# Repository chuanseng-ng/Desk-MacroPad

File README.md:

# Desk MacroPad
 Desk Macro-Pad inspired by PikaTea FK1

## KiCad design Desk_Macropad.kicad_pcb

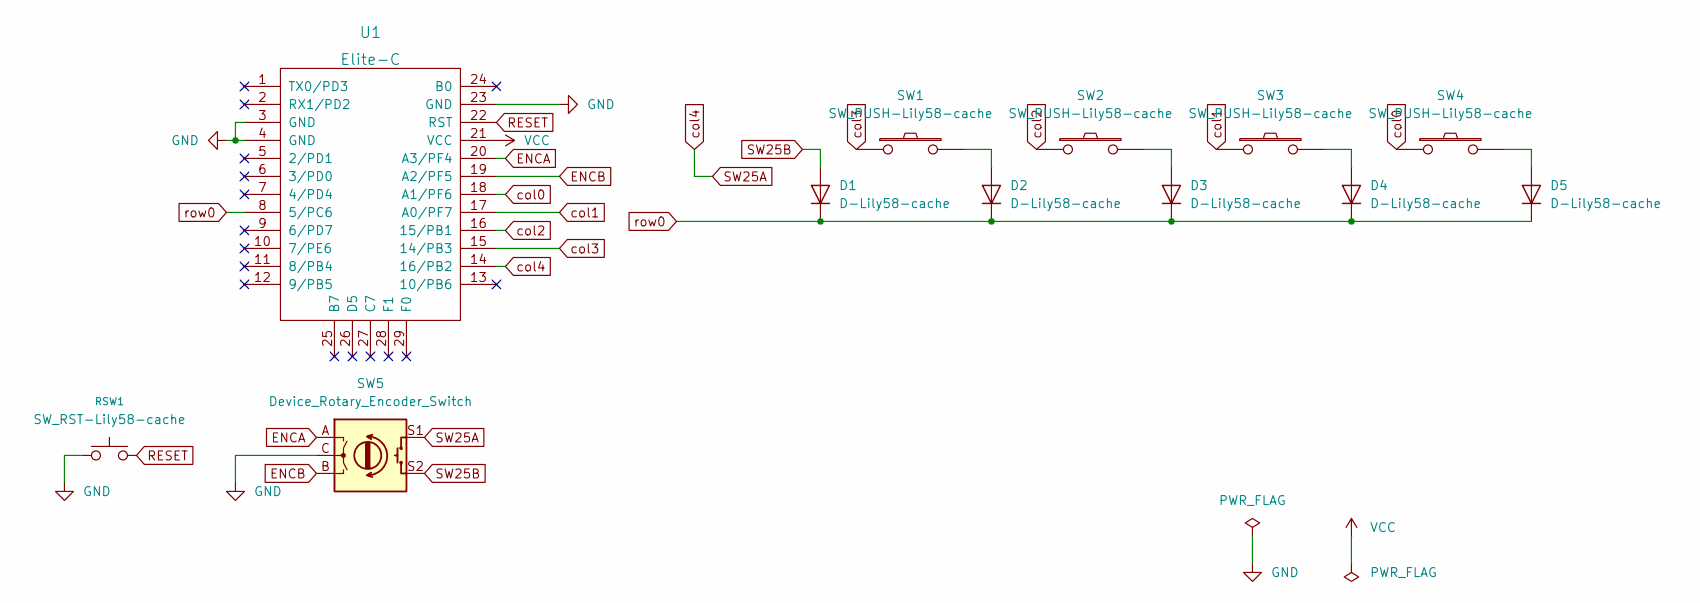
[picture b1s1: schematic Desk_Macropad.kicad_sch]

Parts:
D1, D2, D3, D4, D5: D-Lily58-cache; Diode_SOD123
RSW1: SW_RST-Lily58-cache; TACT_SWITCH_TVBP06
SW1, SW2, SW3, SW4: SW_PUSH-Lily58-cache; CherryMX_Hotswap
SW5: Device_Rotary_Encoder_Switch; RotaryEncoder_Alps_EC11E-Switch_Vertical_H20mm-keebio_modif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
U1: Elite-C

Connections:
ENCA: SW5.A, U1.20 (A3/PF4)
ENCB: SW5.B, U1.19 (A2/PF5)
GND: RSW1.1, SW5.C, U1.3 (GND), U1.4 (GND), U1.23 (GND)
unnamed: D2.2 (A), SW1.2
unnamed: D3.2 (A), SW2.2
unnamed: D4.2 (A), SW3.2
unnamed: D5.2 (A), SW4.2
RESET: RSW1.2, U1.22 (RST)
SW25A: SW5.S1, U1.14 (16/PB2)
SW25B: D1.2 (A), SW5.S2
VCC: U1.21 (VCC)
col0: SW4.1, U1.18 (A1/PF6)
col1: SW3.1, U1.17 (A0/PF7)
col2: SW2.1, U1.16 (15/PB1)
col3: SW1.1, U1.15 (14/PB3)
row0: D1.1 (K), D2.1 (K), D3.1 (K), D4.1 (K), D5.1 (K), U1.8 (5/PC6)

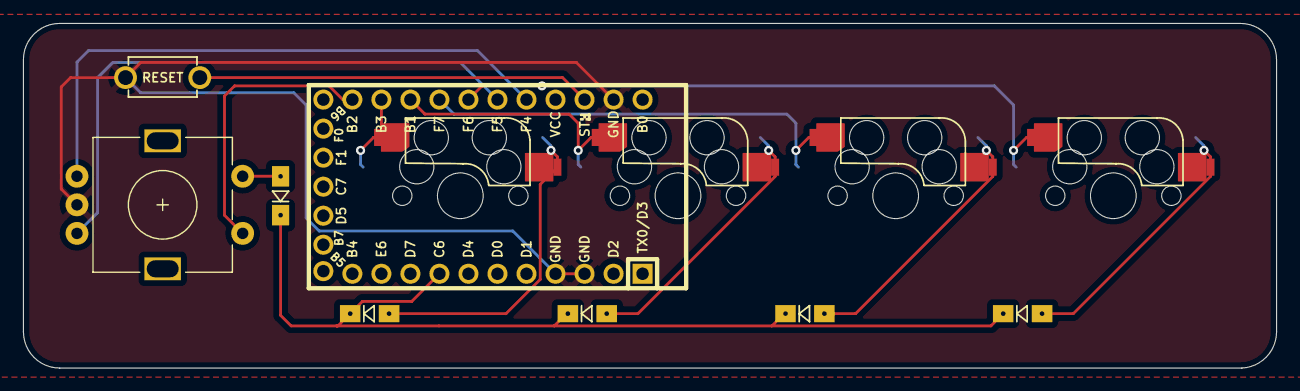
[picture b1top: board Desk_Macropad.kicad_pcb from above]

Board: 2 copper layers, 109.7 x 30.2 mm, 12 parts (1 on the bottom side), 15 nets.

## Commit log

2022-03-12 Initial data push
